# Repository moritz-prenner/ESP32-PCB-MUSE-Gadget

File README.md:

# ESP32 MUSE Gadget 🤖

This project consists of <ins>a custom designed PCB</ins> that consists of:  

| **1x** | SeedStudio ESP32-S3 Board     | [Seedstudio](https://www.seeedstudio.com/XIAO-ESP32S3-p-5627.html) |  
|--------|-------------------------------|---------|  
| **1x** | active Buzzer                 |  myself |  
| **1x** | SH1106 1.3 Inch OLED-Display  |  myself |  
| **4x** | LED-Diode                     |  myself |  
| **4x** | 220 Ohm Resistors             |  myself |  

## INFO ℹ️
This is a custom pcb. it contains leds and a buzzer. it is powered by ai so it should work autonomous.

This project is powered by Muse AI and [the Open Source ESP32 SDK](https://gadgets.muse.ai/)!  
This project is also funded by [Hackclub](https://hackclub.com/)

## WHY ❓

I made this project because I recently heard about this SDK and always wanted to build something that AI autonomous. Also it is easy to make but smart at the same time. Also this is similar to my last pcb i made only a bit mor intense. Thats why i made it.

## PCB 🌟

For the PCB I used KiCad and it will probably be manufactured by JLCPCB!  
These are the pictures of the PCB:

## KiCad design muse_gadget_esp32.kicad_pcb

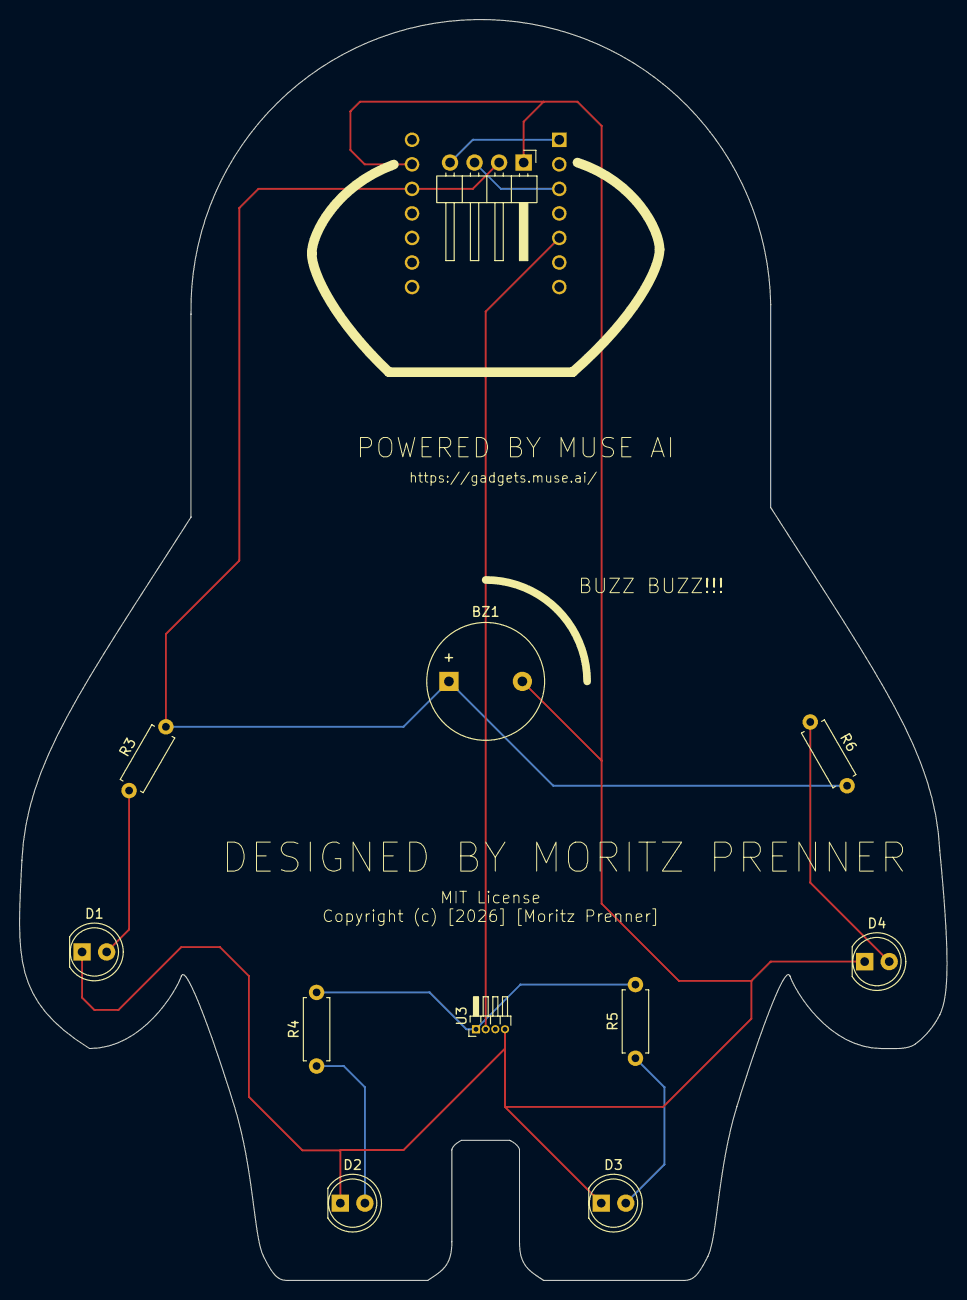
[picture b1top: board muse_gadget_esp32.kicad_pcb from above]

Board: 2 copper layers, 96.0 x 130.5 mm, 12 parts (1 on the bottom side), 9 nets.

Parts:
BZ1: Buzzer; Buzzer_12x9.5RM7.6
D1, D2, D3, D4: D; LED_D5.0mm
R3, R4, R5, R6: 220; R_Axial_DIN0207_L6.3mm_D2.5mm_P7.62mm_Horizontal
U1: XIAO_ESP32_S3; MODULE_XIAO_ESP32_S3
U2: ER_OLEDM0.91_1x-I2C; PinHeader_1x04_P2.54mm_Horizontal
U3: DHT11; PinHeader_1x04_P1.00mm_Horizontal

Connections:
unnamed: BZ1.1 (+), R3.2, R4.2, R5.2, R6.2, U1.12 (3V3), U2.2 (VCC), U3.1 (VDD)
unnamed: BZ1.2 (-), D1.1 (K), D2.1 (K), D3.1 (K), D4.1 (K), U1.13 (GND), U2.1 (GND), U3.4 (GND)
unnamed: D1.2 (A), R3.1
unnamed: D2.2 (A), R4.1
unnamed: D3.2 (A), R5.1
unnamed: D4.2 (A), R6.1
unnamed: U1.1 (D0/GPIO1), U2.4 (SDA)
unnamed: U1.3 (D2/GPIO3), U2.3 (SCL)
unnamed: U1.5 (D4/GPIO5), U3.2 (DATA)

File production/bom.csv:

Designator,Footprint,Quantity,Value,LCSC Part #
BZ1,Buzzer_12x9.5RM7.6,1,Buzzer,
"D1, D2, D3, D4",LED_D5.0mm,4,D,
"R3, R4, R5, R6",R_Axial_DIN0207_L6.3mm_D2.5mm_P7.62mm_Horizontal,4,220,
U1,MODULE_XIAO_ESP32_S3,1,XIAO_ESP32_S3,
U2,PinHeader_1x04_P2.54mm_Horizontal,1,ER_OLEDM0.91_1x-I2C,
U3,PinHeader_1x04_P1.00mm_Horizontal,1,DHT11,

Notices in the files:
muse_gadget_esp32.kicad_pcb:
MIT License
Copyright (c) [2026] [Moritz Prenner]
